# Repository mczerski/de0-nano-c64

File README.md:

# DE0-Nano expansion board for Commodore 64

This board adds necessary interfaces for Commodore 64 implementation from [this](https://github.com/mczerski/c64_DeMiSTify) project.

# Photos

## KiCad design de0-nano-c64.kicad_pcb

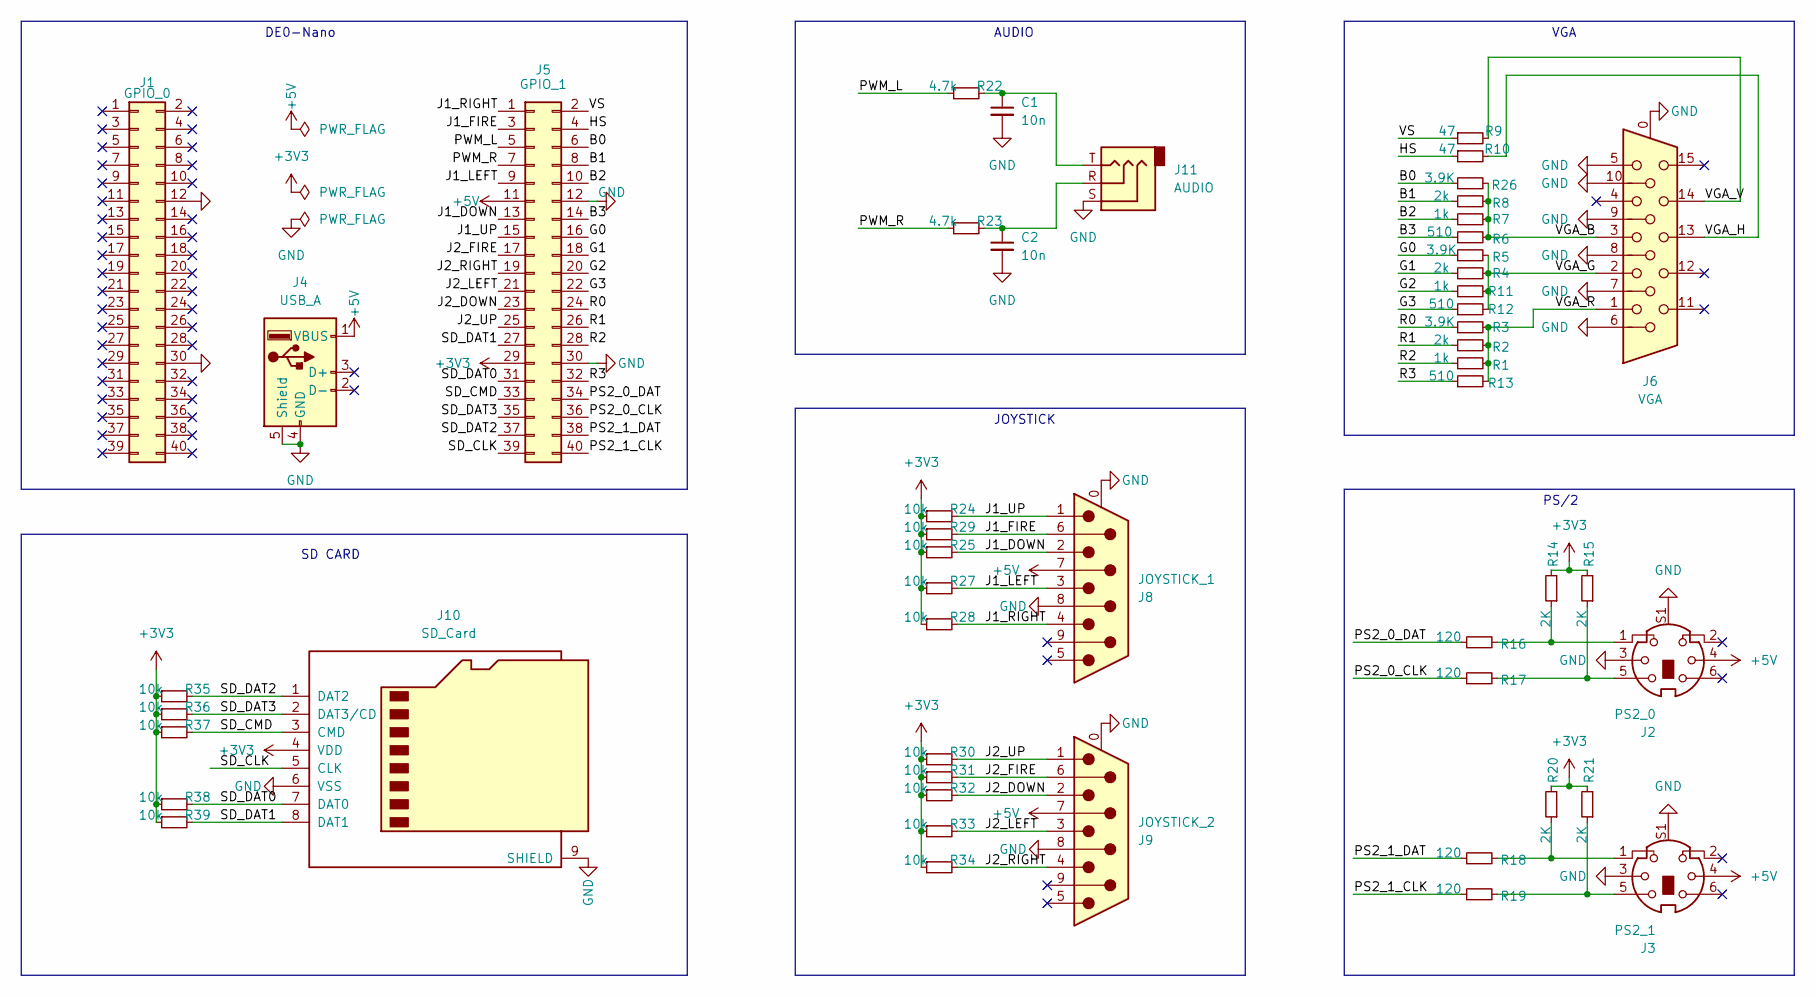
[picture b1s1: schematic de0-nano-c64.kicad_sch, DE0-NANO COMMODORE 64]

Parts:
C1, C2: 10n; C_0603_1608Metric
J1: GPIO_0; PinSocket_2x20_P2.54mm_Polarized_Vertical
J2: PS2_0; CUI_MD-60S
J3: PS2_1; CUI_MD-60S
J4: USB_A; USB_A_Molex_67643_Horizontal
J5: GPIO_1; PinSocket_2x20_P2.54mm_Polarized_Vertical
J6: VGA; AMPHENOL_ICD15S13E4GV00LF
J8: JOYSTICK_1; DSUB-9_Male_Horizontal_P2.77x2.84mm_EdgePinOffset7.70mm_Hou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
J9: JOYSTICK_2; DSUB-9_Male_Horizontal_P2.77x2.84mm_EdgePinOffset7.70mm_Hou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
J10: SD_Card; MOLEX_503398-1892
J11: AUDIO; Jack_3.5mm_CUI_SJ1-3523N_Horizontal
R1, R7, R11: 1k; R_0603_1608Metric
R2, R4, R8: 2k; R_0603_1608Metric
R3, R5, R26: 3.9K; R_0603_1608Metric
R6, R12, R13: 510; R_0603_1608Metric
R9, R10: 47; R_0603_1608Metric
R14, R15, R20, R21: 2K; R_0603_1608Metric
R16, R17, R18, R19: 120; R_0603_1608Metric
R22, R23: 4.7k; R_0603_1608Metric
R24, R25, R27, R28, R29, R30, R31, R32, R33, R34, R35, R36, R37, R38, R39: 10k; R_0603_1608Metric

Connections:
+3V3: J5.29, J10.4 (VDD), R14.2, R15.2, R20.2, R21.2, R24.1, R25.1, R27.1, R28.1, R29.1, R30.1, R31.1, R32.1, R33.1, R34.1, R35.1, R36.1, R37.1, R38.1, R39.1
+5V: J2.4, J3.4, J4.1 (VBUS), J5.11, J8.7, J9.7
/B0: J5.6, R26.1
/B1: J5.8, R8.1
/B2: J5.10, R7.1
/B3: J5.14, R6.1
/G0: J5.16, R5.1
/G1: J5.18, R4.1
/G2: J5.20, R11.1
/G3: J5.22, R12.1
/HS: J5.4, R10.1
/J1_DOWN: J5.13, J8.2, R25.2
/J1_FIRE: J5.3, J8.6, R29.2
/J1_LEFT: J5.9, J8.3, R27.2
/J1_RIGHT: J5.1, J8.4, R28.2
/J1_UP: J5.15, J8.1, R24.2
/J2_DOWN: J5.23, J9.2, R32.2
/J2_FIRE: J5.17, J9.6, R31.2
/J2_LEFT: J5.21, J9.3, R33.2
/J2_RIGHT: J5.19, J9.4, R34.2
/J2_UP: J5.25, J9.1, R30.2
/PS2_0_CLK: J5.36, R17.1
/PS2_0_DAT: J5.34, R16.1
/PS2_1_CLK: J5.40, R19.1
/PS2_1_DAT: J5.38, R18.1
/PWM_L: J5.5, R22.1
/PWM_R: J5.7, R23.1
/R0: J5.24, R3.1
/R1: J5.26, R2.1
/R2: J5.28, R1.1
/R3: J5.32, R13.1
/SD_CLK: J5.39, J10.5 (CLK)
/SD_CMD: J5.33, J10.3 (CMD), R37.2
/SD_DAT0: J5.31, J10.7 (DAT0), R38.2
/SD_DAT1: J5.27, J10.8 (DAT1), R39.2
/SD_DAT2: J5.37, J10.1 (DAT2), R35.2
/SD_DAT3: J5.35, J10.2 (DAT3/CD), R36.2
/VGA_B: J6.3, R6.2, R7.2, R8.2, R26.2
/VGA_G: J6.2, R4.2, R5.2, R11.2, R12.2
/VGA_H: J6.13, R10.2
/VGA_R: J6.1, R1.2, R2.2, R3.2, R13.2
/VGA_V: J6.14, R9.2
/VS: J5.2, R9.1
GND: C1.2, C2.2, J1.12, J1.30, J2.3, J2.S1, J3.3, J3.S1, J4.4 (GND), J4.5 (Shield), J5.12, J5.30, J6.0, J6.5, J6.6, J6.7, J6.8, J6.9, J6.10, J8.0 (PAD), J8.8, J9.0 (PAD), J9.8, J10.6 (VSS), J10.9 (SHIELD), J11.S
unnamed: C1.1, J11.T, R22.2
unnamed: C2.1, J11.R, R23.2
unnamed: J2.1, R14.1, R16.2
unnamed: J2.5, R15.1, R17.2
unnamed: J3.1, R18.2, R20.1
unnamed: J3.5, R19.2, R21.1

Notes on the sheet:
VGA
JOYSTICK
SD CARD
PS/2
DE0-Nano
AUDIO

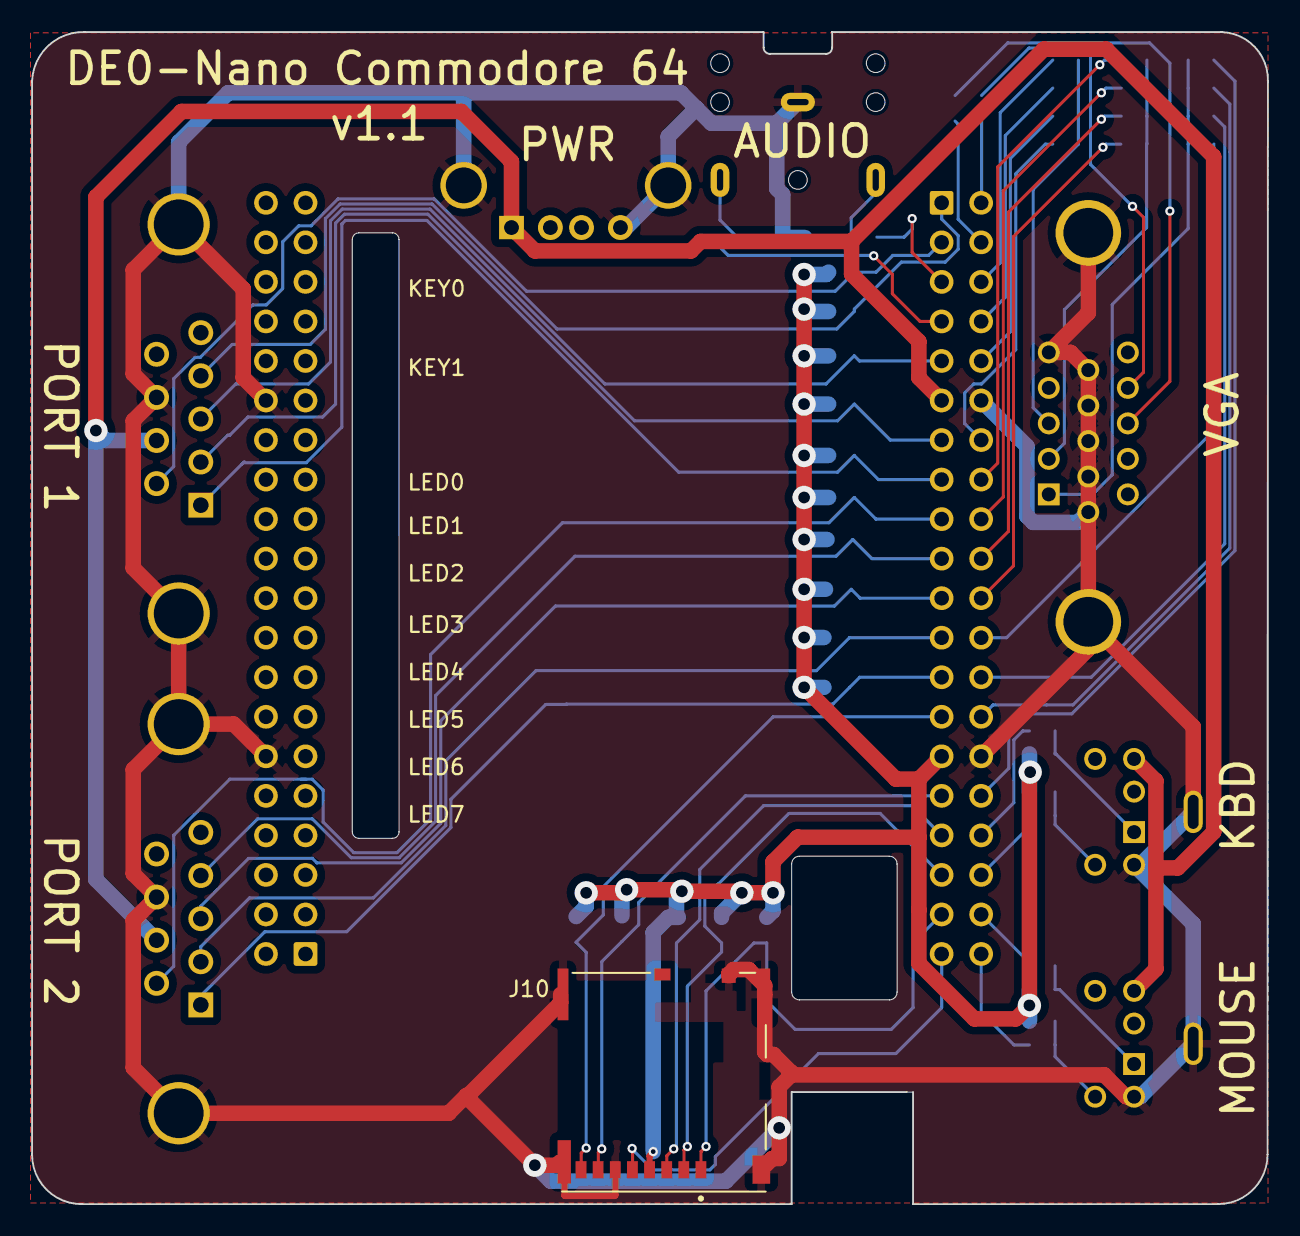
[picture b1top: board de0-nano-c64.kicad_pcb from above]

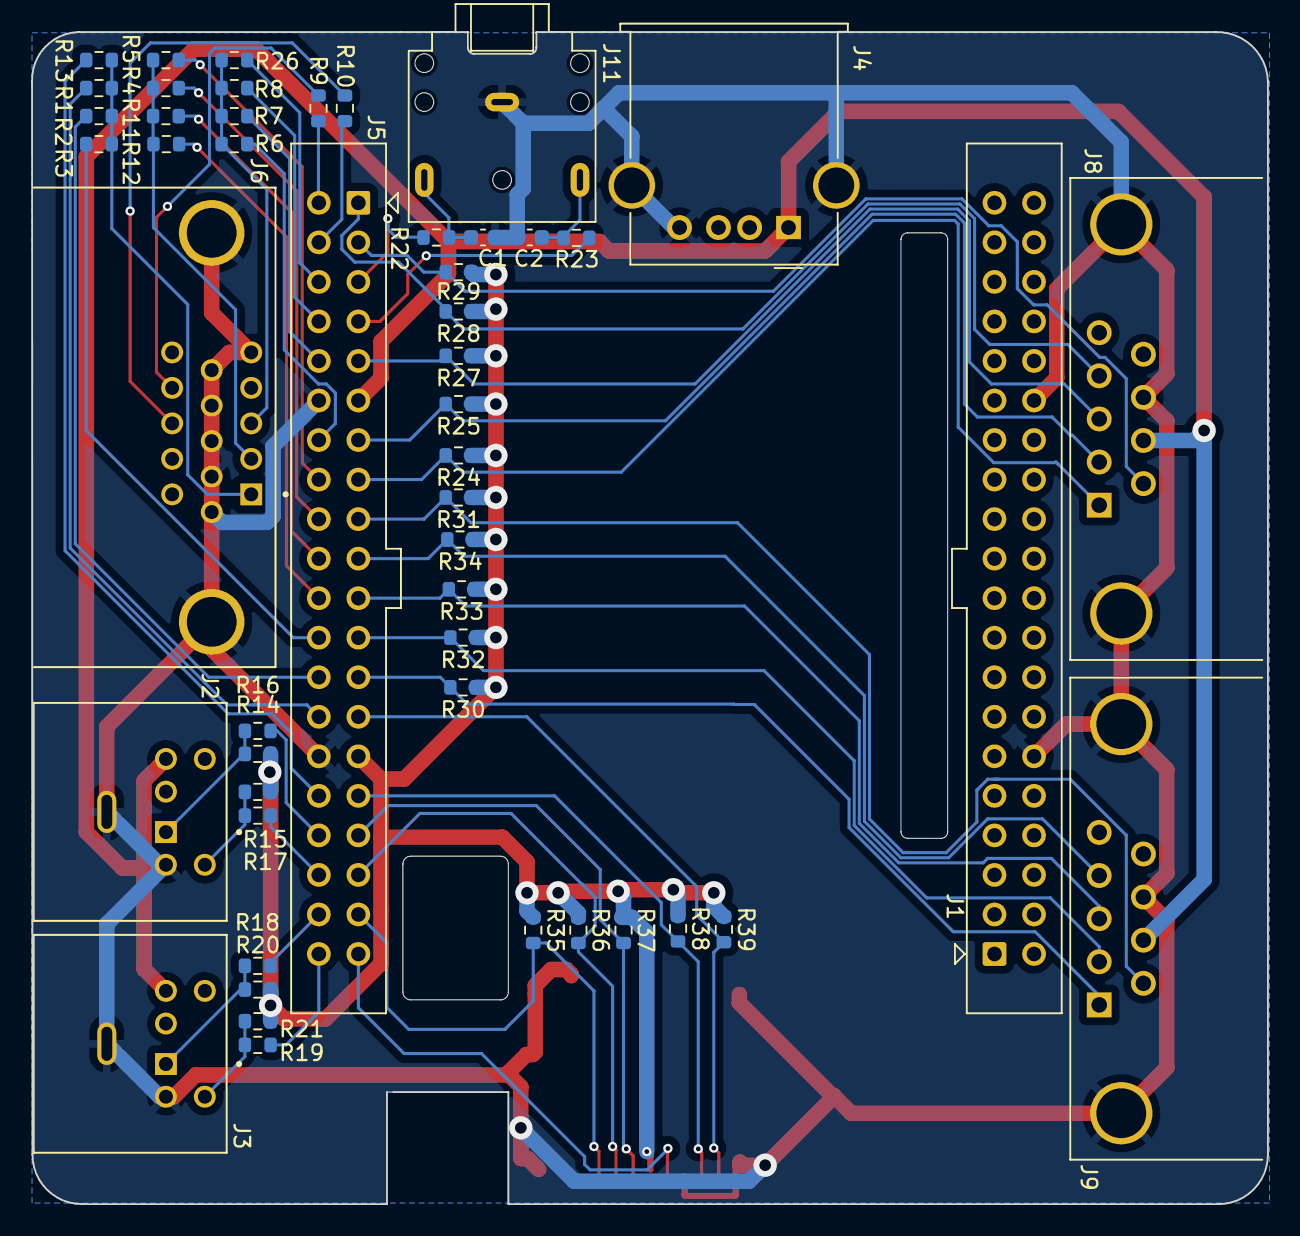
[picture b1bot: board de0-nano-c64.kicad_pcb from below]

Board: 2 copper layers, 79.4 x 75.3 mm, 52 parts (50 on the bottom side), 50 nets.

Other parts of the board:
DE0-Nano: DE0-Nano_bare

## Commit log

2024-01-08 initial
2024-01-08 remove unusedfiles, update footprints and 3d models
2024-01-09 start routing
2024-01-10 finished traces
2024-01-10 finish
2024-01-10 version 1.0
    initial version
    ---------
2024-01-10 add photos
2024-01-10 set gerber export settings for jlcpcb
2024-01-26 reorder some pins due to input only problem
    audio PWM_L/R were assigne to input only pins
2024-12-16 add USB socket for power + add whole cut for dip switches
2024-12-16 update snapshots
